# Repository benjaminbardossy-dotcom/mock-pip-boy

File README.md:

# Overview
The wrist boy is a wrist mounted device containing modules which allow it to take in readings such as the outside temperature, humidity, air pressure, air quality, user heart rate / SpO2 of the user. Readings will be displayed onto a 2.42in I2C OLED, which the player can interact with using the buttons attached. Other features include:\
-2 pairs of LED's acting as straight or perpendicular flashlights\
-A laser pointer(toggled through switches)\
-Vl53l0X module which can measure distance\
-A laser pointer for better accuracy when measuring distance\
-A small speaker + mic\
+Many other software features\
For a more indepth look at the features, see [Features](#features)\
**This design is still a WIP, and many other features are planned. See [The Future of The Wrist Boy](#the-future-of-the-wrist-boy)

# Why I Made This
I was inspired to make this after coming across this project: [The Chip-Boy](https://github.com/hungggryvic/Chip-Boy). Seeing this project, I was inspired to make my own with similar modules.

Despite similar ideas, I had envisioned a few changes to the design, including adding more "survival" based modules. I wanted this device to warn the user if there was any potential danger. To implement this, I added an SpO2 module to measure the users heartrate, an AHT20+BMP280 module for temp and air pressure, an MQ135 module for air quality, and a red LED which would flash if there was any potential danger to the user(E.x. low air quality readings from the MQ135, high temp readings from the AHT20+BMP280.).

However, the idea behind the wrist boy was always the same. I wanted a device able to take in readings from the environment around me, anytime, anywhere, with versatile highly modifiable modules which could easily be coded to fit any need. I wanted a device which could connect to wifi if needed, but run completely off grid whenever necessary as long as it has charge.

After taking into consideration what I wanted from this device, I've created the design below:

# The Design(WIP):

## Features
- **Main Functionality**
   - Custom PCB powered by an ESP32 module which serves as the heart of the device as it handles all firmware
   - Responsive user interface, which is displayed on an 2.42 inch OLED screen, and can be interacted with through the attached switches
   - Rechargeable LIPO battery which can be charged through the attached TP4056 module.
   - laser which toggles on for accurate measurement when using the VL53L0X, or can alternatively be toggled through the second switch attached
   - 2 pairs of LED's which function as flashlights for the user, and are toggled through the attached switches
   - Micro SD card reader module which function as extended storage for the ESP32. For this device it stores music data, which can then be played on the attached speaker.
- **Environmental Data Gathering**
   - MAX30102 module to measure the users heatrate
   - MQ135 module to measure general air quality
   - AHT20+BMP280 to measure environmental temperature and air pressure
   - VL53L0X module for accurately measuring distance to the nearest mm
- **Audio**
   - Small speaker to play music or other audio
   - Small microphone which takes in audio and can be used to program a variety of features, such as voice activated commands
   - A piezo buzzer which adds depth to the interface by playing different frequency beeps depending on user input

## The Case
\
I designed a case to mount the PCB to, which could then slip onto the user's wrist. The case features two separate pieces which snap together to ease 3D printing and reduce support generation where possible. The PCB itself mounts to the case through the use of M2 screws. The case features 4 small holes in each corner to place M2 heat inserts into, which then mount the PCB in place by screwing in 4 M2 screws into the 4 corners of the PCB. The case includes a small rectangular hole near the bottom, which the SpO2 module slots into, before the wires are strung through the hollow case and connected to the PCB. This allows proper heart rate readings to be read, as the module is lightly pressed into the user's wrist at constant pressure. The case also includes holes for both the MQ135 and AHT20+BMP280, allowing the sensors to fit into the case and under the PCB.

## The PCB
\
The PCB features a 2 layer design, with a track size of 0.25mm, and an overall sizing of 67x107mm. The microcontroller used was the ESP32. which is soldered directly to the board. The OLED screen is quite large, sitting at 48x70mm, and for this reason it is mounted to female headers, allowing it to sit overtop of the ESP32 and other components. The two pairs of LED's sit off the board, acting as flashlights.
## 3D View:
\

## Wiring Schematic

This wiring schematic is identical to the routing on the PCB, but shown in greater detail.

# Assembling Your Own
If you're interested in creating your own wrist boy, the simplified construction of the wrist boy is as follows:
1. Gather the necessary files(All files / folders referenced can be found at the top of this repo):
   - Download the step files found in folder labeled CAD Models
   - Download the zip file containing the gerber files for the PCB labeled wrist_boy_gerber.zip, found in the folder labeled PCB
2. Gather the Parts
   - See the BOM below and order any parts you don't already have using the links provided
   - Go to JLCPCB and start a new order
   - Drag and drop wrist_boy_gerber.zip into the file uploader
   - Submit the order
   - Upload the step files to a 3D printing application of your choice and print the models OR upload the step files to JLCPCB's 3D printing service and add to your existing PCB order if you don't have access to a 3D printer
3. Assemble
   - Solder components to the board following the rules below and using the schematic as reference
      - make sure to solder a 4 pin female header instead of the screen to the designated OLED pins on the board
      - Do not solder the aht20+bmp280, MQ135, laser pointer, or MAX30102 directly to the board
   - Place the MAX30102 into its designated slot near the bottom of the case, placing the wires through the case
   - Superglue the connecting pieces of the 3D printed case together and let set
   - Place the MQ135 and aht20+bmp280 into their places in the case, securing with M2 screws and nuts
   - Optionally mount the laser pointer to the top of the VL53l0X
   - Use the solder gun to melt the M2 heat inserts into the case in the holes located at each corner of the case
   - Place battery into the case and secure with double sided tape
   - Place the PCB on top of the case in line with the holes
   - Using M2 screws, secure the PCB to the case
4. Firmware
   - Download the code using the provided ino file wristboy_untested.ino
   - Plug the ESP32 in, and connect to whatever device you're using to upload the code
   - Upload the code to the ESP32

## BOM
| Material      | Quantity      | Cost($CAD)     | Link          |
| ------------- | ------------- | ------------- | ------------- |
| M2 Screws | 10 | 0.21 | https://www.amazon.ca/780Pcs-Screws-Metric-Washers-Steel-Black/dp/B0D7QCS5FL?source=ps-sl-shoppingads-lpcontext&ref_=fplfs&smid=A3GSZ4RKHEJUDQ&th=1 |
| M2 Nuts | 6 | 0.12 | https://www.amazon.ca/780Pcs-Screws-Metric-Washers-Steel-Black/dp/B0D7QCS5FL?source=ps-sl-shoppingads-lpcontext&ref_=fplfs&smid=A3GSZ4RKHEJUDQ&th=1 |
| M2 Heat Inserts | 4 | 0.56 | https://www.amazon.ca/HANGLIFE-Heat-Set-Threaded-Components-Soldering/dp/B0D477R64K?th=1 |
| ESP32         | 1             |   10.99       |    https://www.amazon.ca/ELEGOO-ESP-WROOM-32-Development-Bluetooth-Microcontroller/dp/B0D8T7Z1P5?th=1           |
| Mini Step-Up Boost Converter | 1 | 3.66 | https://www.amazon.ca/CANADUINO%C2%AE-DC-DC-Step-Up-Converter-2-5-5V/dp/B09TZSGHYK/ref=asc_df_B09TZSGHYK?mcid=829455ac296e3eefbfeefdcb151b2f70&tag=googleshopc0c-20&linkCode=df0&hvadid=706724917107&hvpos=&hvnetw=g&hvrand=10632712767633782168&hvpone=&hvptwo=&hvqmt=&hvdev=c&hvdvcmdl=&hvlocint=&hvlocphy=9000685&hvtargid=pla-2298538843345&psc=1&hvocijid=10632712767633782168-B09TZSGHYK-&hvexpln=0&gad_source=4 |
| 3.7V 18650A 2000mAh LIPO Battery | 1 | 8.63 | https://www.aliexpress.com/item/1005010527559361.html?spm=a2g0o.order_list.order_list_main.5.46711802fXqOzT |
| 5 Way Switch | 1 | 0.88 | https://www.aliexpress.com/item/4000681560472.html?spm=a2g0o.order_list.order_list_main.44.46711802fXqOzT |
| Mini Laser Pointer | 1 | 0.66 | https://www.aliexpress.com/item/1005009410058180.html?spm=a2g0o.order_list.order_list_main.50.46711802fXqOzT |
| 2.42 inch OLED Display  | 1 | 13.58  | https://www.aliexpress.com/item/4000002579405.html?spm=a2g0o.order_list.order_list_main.61.46711802fXqOzT |
| TP4056 Lithium Battery Charger Module | 1 | 0.47 | https://www.aliexpress.com/item/32930640893.html?spm=a2g0o.order_list.order_list_main.71.46711802fXqOzT |
| VL53L0X Module | 1 | 5.69 | https://www.aliexpress.com/item/1005008798415699.html?spm=a2g0o.order_list.order_list_main.191.49da1802f3M5CC |
| MAX30102 Module | 1 | 3.07 | https://www.aliexpress.com/item/1005007015407514.html?spm=a2g0o.order_list.order_list_main.56.64ef1802V6ZYNr |
| MQ135 Module | 1 | 5.09 | https://www.aliexpress.com/item/1005009467470672.html?spm=a2g0o.order_list.order_list_main.91.46711802fXqOzT |
| AHT20+BMP280 Module | 1 | 4.89 | https://www.aliexpress.com/item/1005005982427374.html?spm=a2g0o.order_list.order_list_main.96.46711802fXqOzT |
| Mini Slide Switch 3pin | 3 | 0.37 | https://www.aliexpress.com/item/1005005633418066.html?spm=a2g0o.order_list.order_list_main.171.46711802fXqOzT |
| Micro Push Button | 2 | 0.10 | https://www.aliexpress.com/item/32815969627.html?spm=a2g0o.order_list.order_list_main.196.46711802fXqOzT |
| Led Diode, 3mm 5mm | 5 | 0.35 | https://www.aliexpress.com/item/1005007214694188.html?spm=a2g0o.order_list.order_list_main.226.46711802fXqOzT |
| Resistors | 10 | 0.06 | https://www.aliexpress.com/item/1005005855324735.html?spm=a2g0o.order_list.order_list_main.241.46711802fXqOzT |
| INMP441 Module | 1 | 5.89 | https://www.aliexpress.com/item/1005011560363321.html?spm=a2g0o.detail.0.0.128fDWY0DWY0No&mp=1&pdp_npi=6%40dis%21CAD%21CAD+11.78%21CAD+5.89%21%21CAD+5.36%21%21%21%402103128917777614208214544eb8e6%2112000055922209462%21ct%21CA%216516785883%21%211%210%21 |
| Micro SD Card Module | 1 | 3.71 | https://www.aliexpress.com/item/1005010519562186.html?spm=a2g0o.detail.0.0.6565Ol4TOl4TF1&mp=1&pdp_npi=6%40dis%21CAD%21CAD+9.08%21CAD+3.71%21%21CAD+3.38%21%21%21%402101e2b417777604375576021e62d1%2112000052676608865%21ct%21CA%216516785883%21%211%210%21 |
| MAX98357A Module | 1 | 3.07  | https://www.aliexpress.com/item/1005007068815767.html?spm=a2g0o.detail.0.0.6565Ol4TOl4TF1&mp=1&pdp_npi=6%40dis%21CAD%21CAD+3.07%21CAD+3.07%21%21CAD+2.82%21%21%21%402101e2b417777604375576021e62d1%2112000056349468594%21ct%21CA%216516785883%21%211%210%21 |
| 8Ohm 1W Speaker | 1 | 4.82 | https://www.aliexpress.com/item/1005011920753806.html?spm=a2g0o.detail.0.0.6565Ol4TOl4TF1&mp=1&pdp_npi=6%40dis%21CAD%21CAD+9.84%21CAD+4.82%21%21CAD+4.39%21%21%21%402101e2b417777604375576021e62d1%2112000057040904678%21ct%21CA%216516785883%21%211%210%21 |
| Piezo Buzzer | 1 | 0.27 | https://www.aliexpress.com/item/1005006260328559.html?spm=a2g0o.productlist.main.4.1cee40902qEetf&aem_p4p_detail=20260502153430362601419017360005695929&algo_pvid=9c8b0b99-3bbf-419b-8874-6d4fe906f763&algo_exp_id=9c8b0b99-3bbf-419b-8874-6d4fe906f763-3&pdp_ext_f=%7B%22order%22%3A%221007%22%2C%22spu_best_type%22%3A%22price%22%2C%22eval%22%3A%221%22%2C%22fromPage%22%3A%22search%22%7D&pdp_npi=6%40dis%21CAD%211.51%211.36%21%21%211.09%210.98%21%402101eede17777612699931507ec38b%2112000036509108003%21sea%21CA%216516785883%21X%211%210%21n_tag%3A-29919%3Bd%3Ab1c396d5%3Bm03_new_user%3A-29895&curPageLogUid=fZmKYKihIY1A&utparam-url=scene%3Asearch%7Cquery_from%3A%7Cx_object_id%3A1005006260328559%7C_p_origin_prod%3A&search_p4p_id=20260502153430362601419017360005695929_1 |

# The Future of The Wrist Boy
This design is not final, and I plan on refining the PCB and case alot more in the future. I plan on having a fully integrated circuit with no prebuilt modules, which woiuld save space and allow me to build a full case which encloses the hardware, and I also plan on changing and refining the code as I test the hardware. Another large modification I have planned is the addition of a 5V solar panel to charge the battery, attached to a custom PCB which allows both USB-C charging and solar charging.

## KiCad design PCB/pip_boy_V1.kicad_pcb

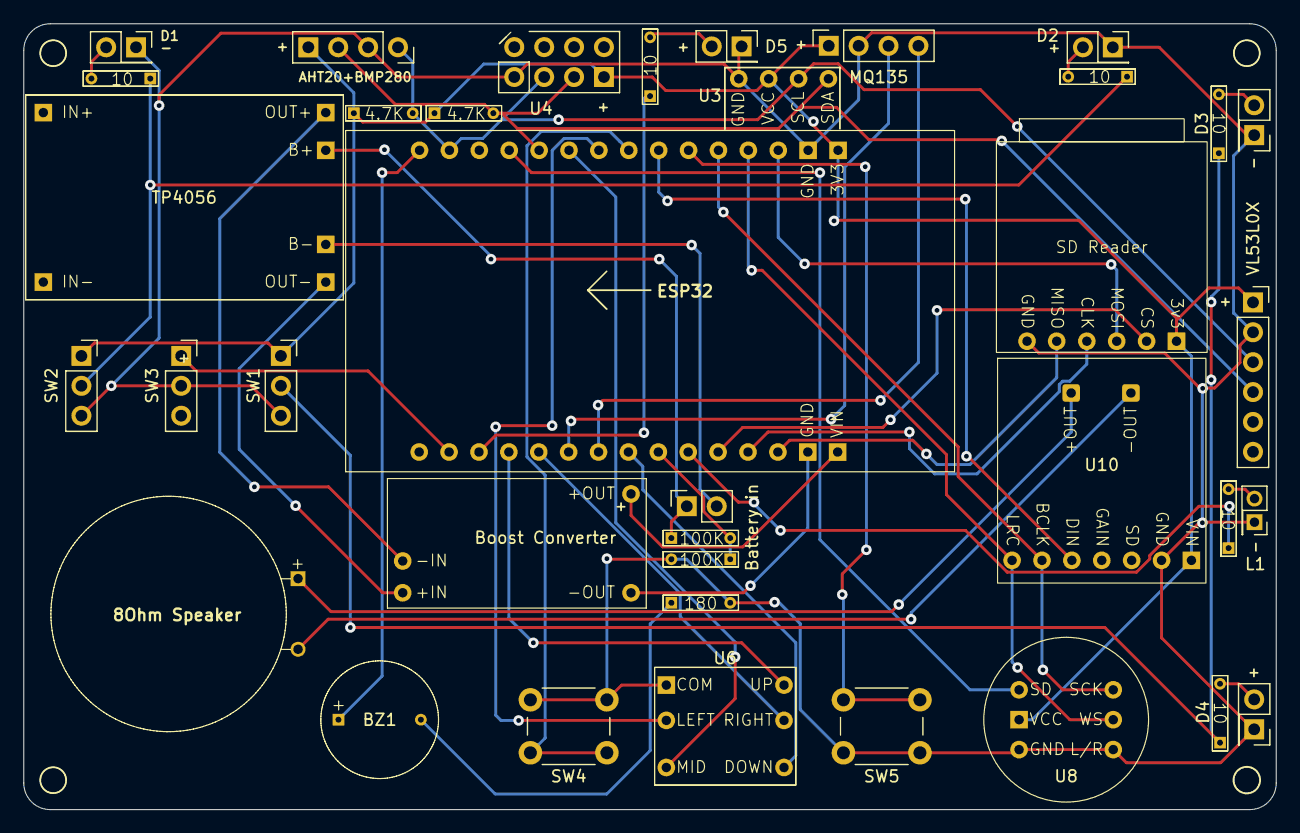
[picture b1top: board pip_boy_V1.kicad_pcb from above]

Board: 4 copper layers, 106.4 x 66.8 mm, 37 parts (0 on the bottom side), 43 nets.

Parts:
BZ1: Buzzer; Piezo_buzzer_D10mm
Battery in: Battery in; PinSocket_1x02_P2.54mm_Vertical
D1, D2, D3, D4, D5: LED; PinSocket_2x01_P2.54mm_Vertical
L1: LASER; PinSocket_2x01_P2.00mm_Vertical
MQ135: MQ135; PinSocket_1x04_P2.54mm_Vertical
R1, R2, R3, R4, R5, R6: 10; Resistor_THT_L5.00mm_D1.0mm
R7, R8: 100K; Resistor_THT_L5.00mm_D1.0mm
R9: 180; Resistor_THT_L5.00mm_D1.0mm
R10, R11: 4.7K; Resistor_THT_L5.00mm_D1.0mm
S1: Speaker; 8Ohm_1W_20mm_speaker
SD Reader: SD Reader; micro_SD_card_module
SW1, SW2, SW3: SW_SPDT; PinSocket_1x03_P2.54mm_Vertical
SW4, SW5: SW_Push; SW_PUSH_6mm_H4.3mm
U1: ESP32; ESP32_elegoo
U3: SSD1309; SSD1309(4_pin)
U4: MAX30102; PinSocket_2x04_P2.54mm_Vertical
U5: AHT20+BMP280; PinSocket_1x04_P2.54mm_Vertical
U6: 5 way switch; 5_way_switch
U8: INMP441
U10: MAX98357A
U12: TP4056; TP4056_module
U13: Boost Converter; mini_step-up_boost_converter
VL53L0X: VL53L0X; PinSocket_1x06_P2.54mm_Vertical

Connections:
+3.3V: MQ135.1 (VIN), R10.1, R11.1, SD Reader.1 (VIN), SW1.1 (A), SW2.1 (A), U1.2 (3V3), U3.1 (VIN), U4.1 (VIN), U5.1 (VIN), U8.1 (VIN), U10.1 (VIN), VL53L0X.1 (VIN)
AO1: MQ135.4 (AO), U1.9 (GPIO33)
B1: U1.6 (GPIO34), U6.4 (UP)
B2: U1.7 (GPIO35), U6.5 (RIGHT)
B3: U1.10 (GPIO25), U6.6 (DOWN)
B4: U1.30 (GPIO18), U6.2 (LEFT)
B5: U1.31 (GPIO19), U6.3 (MID)
B6: SW5.1, U1.27 (GPIO16)
B7: SW4.1, U1.29 (GPIO5)
Battery_in: Battery in.1 (+Out), R8.1, U12.5 (B+)
DO1: MQ135.3 (DO), U1.8 (GPIO32)
GND: D1.1 (K), D2.1 (K), D3.1 (K), D4.1 (K), D5.1 (K), L1.1 (K), MQ135.2 (GND), R7.2, R9.2, SD Reader.2 (GND), SW1.3 (C), SW2.3 (C), SW3.2 (B), SW4.2, SW5.2, U1.38 (GND), U3.2 (GND), U4.2 (GND), U5.2 (GND), U6.1 (COM), U8.2 (GND), U8.4 (L/R), U10.2 (GND), VL53L0X.2 (GND)
GPIO2: U1.24 (GPIO2), U8.5 (WS), U10.3 (LRC)
GPIO3: U1.34 (GPIO3), U8.3 (SD)
GPIO4: U1.26 (GPIO4), U8.6 (SCK), U10.4 (BCLK)
GPIO12: SD Reader.5 (CLK), U1.14 (GPIO12)
GPIO13: SD Reader.6 (MISO), U1.16 (GPIO13)
GPIO14: SD Reader.3 (CS), U1.13 (GPIO14)
GPIO15: SD Reader.4 (MOSI), U1.23 (GPIO15)
GPIO17: U1.28 (GPIO17), U10.5 (DIN)
GPIO23: BZ1.1 (+), U1.37 (GPIO23)
GPIO26: R7.1, R8.2, U1.11 (GPIO26)
GPIO27: R6.1, U1.12 (GPIO27)
GPIO36: SW3.1 (A), U1.4 (GPIO36)
GPIO39: R5.1, U1.5 (GPIO39)
unnamed: BZ1.2 (-), R9.1
unnamed: D1.2 (A), R2.2
unnamed: D2.2 (A), R1.2
unnamed: D3.2 (A), R3.2
unnamed: D4.2 (A), R4.2
unnamed: D5.2 (A), R5.2
unnamed: L1.2 (A), R6.2
unnamed: R3.1, R4.1, SW1.2 (B)
unnamed: R1.1, R2.1, SW2.2 (B)
unnamed: S1.1, U10.8 (+OUT)
unnamed: S1.2, U10.9 (-OUT)
unnamed: Battery in.2 (-Out), U12.6 (B-)
unnamed: U12.3 (+out), U13.1 (-IN)
unnamed: U12.4 (-out), U13.2 (+IN)
Power+: U1.0 (VIN), U13.3 (+OUT)
Power-: U1.1 (GND), U13.4 (-OUT)
SCL: R11.2, U1.36 (GPIO22), U3.3 (SCL), U4.4 (SCL), U5.4 (SCL), VL53L0X.3 (SCL)
SDA: R10.2, U1.33 (GPIO21), U3.4 (SDA), U4.3 (SDA), U5.3 (SDA), VL53L0X.4 (SDA)

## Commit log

2026-04-16 Enhance README with detailed device description
    Updated project description to include device features and functionalities.
2026-04-16 Refactor README for better clarity and structure
2026-04-16 Fix formatting issues in README.md
2026-04-19 Create Parts List
2026-04-19 Update Parts List
2026-04-19 Rename Parts List to Parts_List.md
2026-04-19 Change line breaks to HTML in Parts_List.md
    Updated formatting for parts list to use HTML line breaks.
2026-04-19 Format parts list header as bold
2026-04-19 Update parts list formatting and add components
2026-04-19 Fix links in Parts_List.md
    Updated links for resistors and LEDs in the parts list.
2026-04-19 Fix markdown link formatting in README.md
2026-04-19 Update Parts_List.md
    Added SPO2 module to the parts list.
2026-04-30 Add initial firmware files and necessary libraries
2026-05-02 Update Firmware(untested)
2026-05-02 Add schematic image to KiCad_Schematic.md
2026-05-02 Add header for KiCad schematic image
2026-05-02 Create Wrist_left
2026-05-02 Add placeholder for Wrist_left CAD model
2026-05-02 Rename wristboy_KiCad.zip to PCB/Full Project Zip File
2026-05-02 Add KiCad PCB image to documentation
2026-05-02 Rename KiCad Images.md to PCB/KiCad Images.md
2026-05-02 Revise README with new project name and details
    Updated project name and expanded device features. Added photos and BOM with materials and links.
2026-05-02 Add new modules and update prices in README
2026-05-02 Clean up BOM entries in pip_boy_V1.csv
    Removed old component data from the BOM.
2026-05-02 Add comments for code purpose and libraries
    Added comments explaining the purpose of the code and libraries used.
2026-05-15 Create Fusion 360 Source File
2026-05-15 Rename wrist_boy_V1.f3z to Fusion 360 Source File/wrist_boy_V1.f3z
